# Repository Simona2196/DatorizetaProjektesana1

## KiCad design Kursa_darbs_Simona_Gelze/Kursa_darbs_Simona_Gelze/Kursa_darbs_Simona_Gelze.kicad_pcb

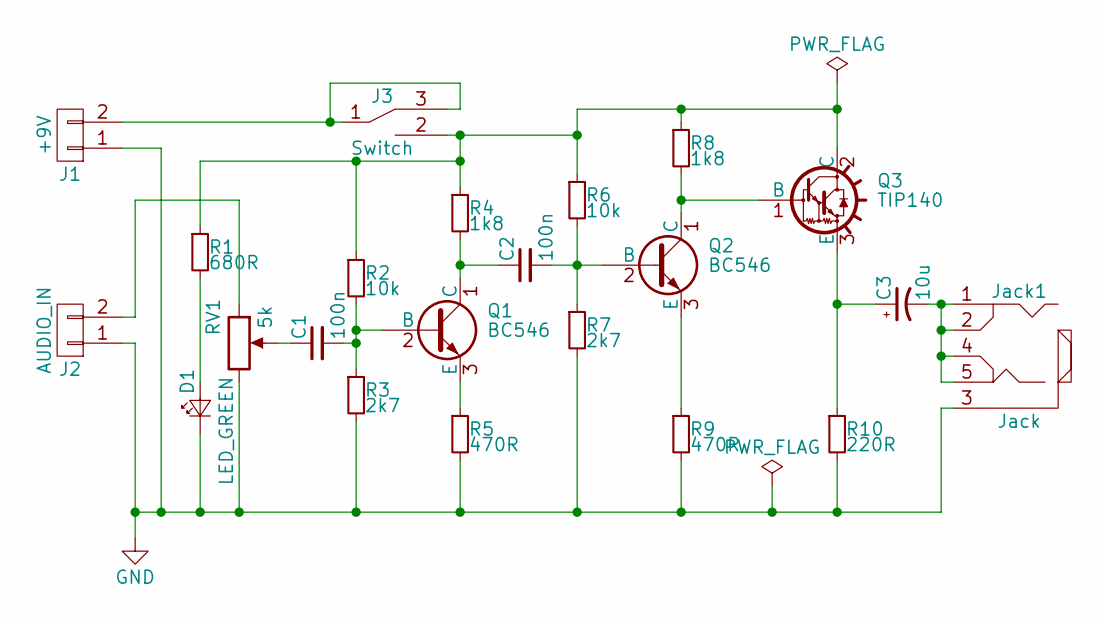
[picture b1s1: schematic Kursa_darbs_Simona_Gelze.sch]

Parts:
C1, C2: 100n; C_Disc_D5.0mm_W2.5mm_P2.50mm
C3: 10u; CP_Radial_Tantal_D7.0mm_P5.00mm
D1: LED_GREEN; LED_D5.0mm
J1: +9V; TerminalBlock_Pheonix_MKDS1.5-2pol
J2: AUDIO_IN; audio_input_conn
J3: Switch; SW_SPDT
Jack1: Jack; AUDIO_JACK
Q1, Q2: BC546; TO-92_Molded_Narrow
Q3: TIP140; TO-220_Vertical
R1: 680R; R_Axial_DIN0204_L3.6mm_D1.6mm_P7.62mm_Horizontal
R2, R6: 10k; R_Axial_DIN0204_L3.6mm_D1.6mm_P7.62mm_Horizontal
R3, R7: 2k7; R_Axial_DIN0204_L3.6mm_D1.6mm_P7.62mm_Horizontal
R4, R8: 1k8; R_Axial_DIN0204_L3.6mm_D1.6mm_P7.62mm_Horizontal
R5, R9: 470R; R_Axial_DIN0204_L3.6mm_D1.6mm_P7.62mm_Horizontal
R10: 220R; R_Axial_DIN0204_L3.6mm_D1.6mm_P7.62mm_Horizontal
RV1: 5k; Potentiometer_WirePads

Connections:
GND: D1.1 (K), J1.1, J2.1, Jack1.3, R3.2, R5.2, R7.2, R9.2, R10.2, RV1.3
unnamed: C1.1, RV1.2
unnamed: C1.2, Q1.2 (B), R2.2, R3.1
unnamed: C2.1, Q1.1 (C), R4.2
unnamed: C2.2, Q2.2 (B), R6.2, R7.1
unnamed: C3.1, Q3.3 (E), R10.1
unnamed: C3.2, Jack1.1, Jack1.2, Jack1.4, Jack1.5
unnamed: D1.2 (A), R1.2
unnamed: J1.2, J3.1, J3.3
unnamed: J2.2, RV1.1
unnamed: J3.2, Q3.2 (C), R1.1, R2.1, R4.1, R6.1, R8.1
unnamed: Q1.3 (E), R5.1
unnamed: Q2.1 (C), Q3.1 (B), R8.2
unnamed: Q2.3 (E), R9.1

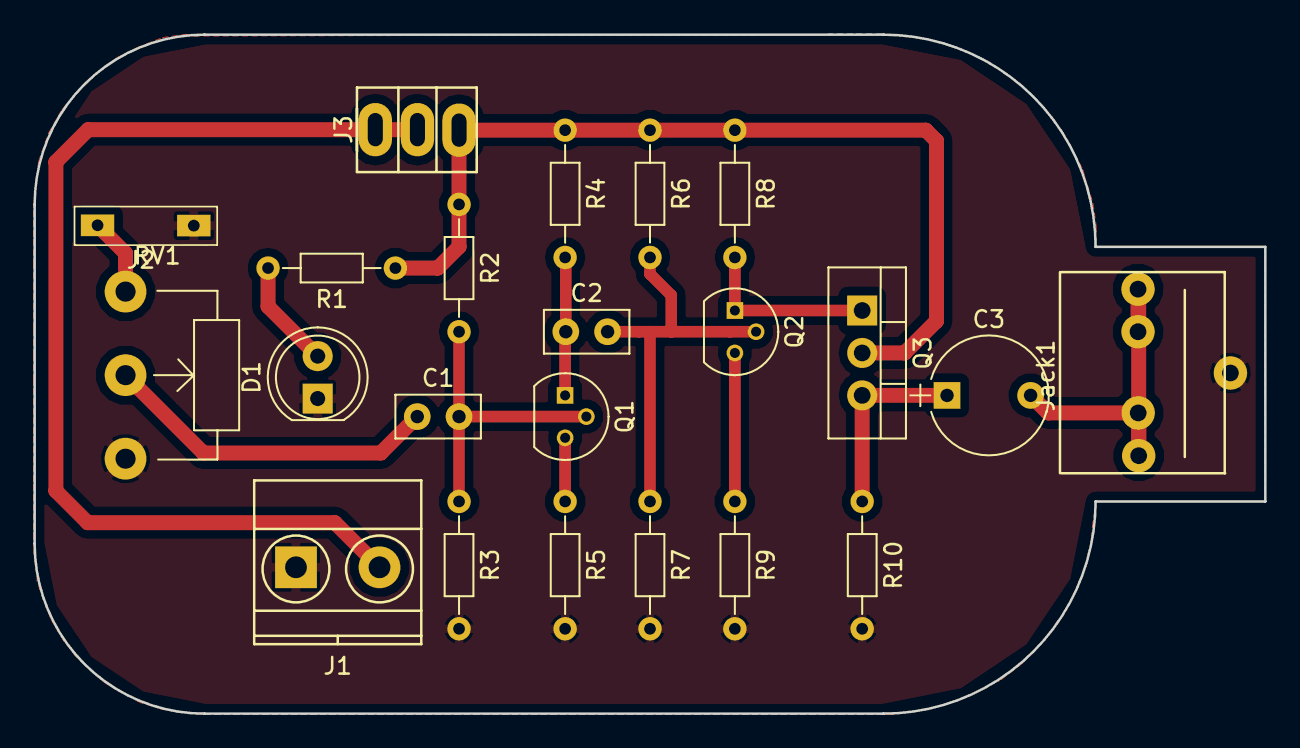
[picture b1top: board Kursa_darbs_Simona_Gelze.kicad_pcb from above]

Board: 2 copper layers, 73.7 x 40.6 mm, 22 parts (0 on the bottom side), 14 nets.

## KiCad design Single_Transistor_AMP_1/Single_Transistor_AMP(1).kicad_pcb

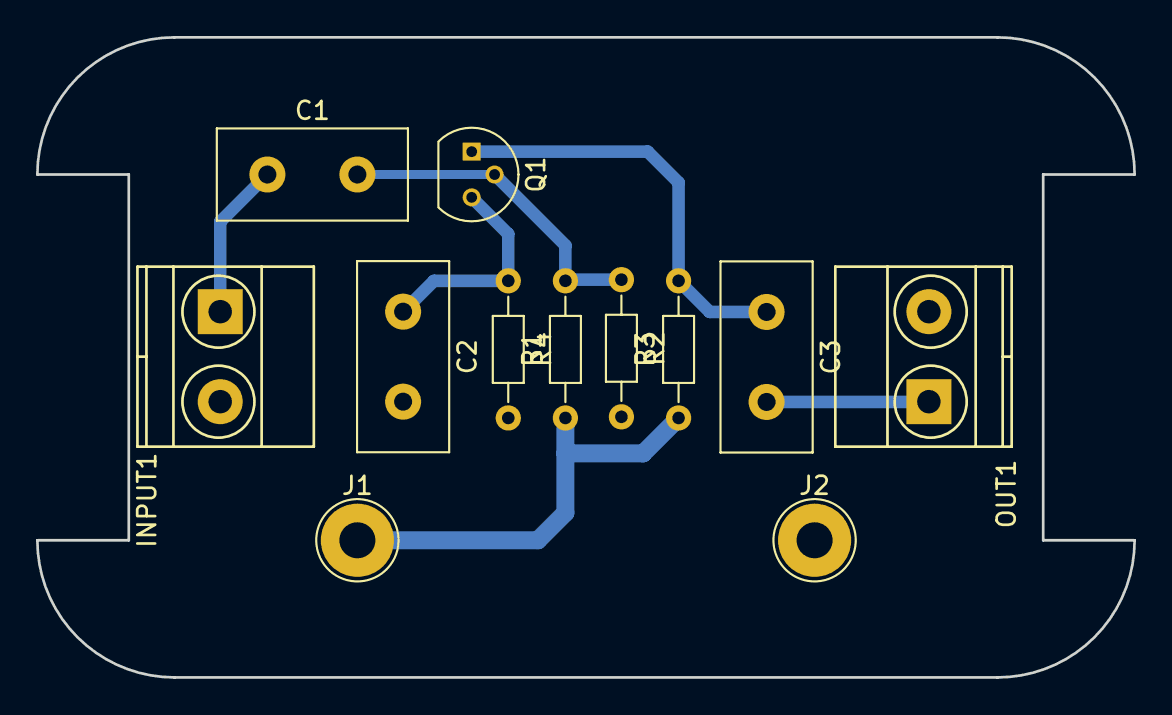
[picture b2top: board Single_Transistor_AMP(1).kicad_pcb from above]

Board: 2 copper layers, 61.0 x 35.6 mm, 12 parts (0 on the bottom side), 7 nets.

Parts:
C1, C3: 20uF; C_Disc_D10.5mm_W5.0mm_P5.00mm
C2: 50uF; C_Disc_D10.5mm_W5.0mm_P5.00mm
INPUT1: SIGNAL; TerminalBlock_Pheonix_MKDS1.5-2pol
J1: +12V; 1pin
J2: GND; 1pin
OUT1: Signal; TerminalBlock_Pheonix_MKDS1.5-2pol
Q1: BC548; TO-92_Molded_Narrow
R1: 22k; R_Axial_DIN0204_L3.6mm_D1.6mm_P7.62mm_Horizontal
R2: 6,8k; R_Axial_DIN0204_L3.6mm_D1.6mm_P7.62mm_Horizontal
R3: 4,7k; R_Axial_DIN0204_L3.6mm_D1.6mm_P7.62mm_Horizontal
R4: 1,8k; R_Axial_DIN0204_L3.6mm_D1.6mm_P7.62mm_Horizontal

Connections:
+12V: J1.1, R1.1, R3.1
GND: C2.2, INPUT1.2, J2.1, OUT1.2, R2.2, R4.2
unnamed: C1.1, INPUT1.1
unnamed: C1.2, Q1.2, R1.2, R2.1
unnamed: C2.1, Q1.3, R4.1
unnamed: C3.1, Q1.1, R3.2
unnamed: C3.2, OUT1.1

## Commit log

2017-06-16 Testa fails
2017-06-16 Batterry holder
2017-06-16 Gerbera faili
2017-06-16 Power supply
2017-06-16 Single transistor amp
2017-06-16 Single transistor amp1
2017-06-16 Single transistor amplifier pecapstrade
2017-06-16 Multivibrators
2017-06-17 Kursa darbs,austiņu pastiprinātājs uz diskrētiem elementiem
